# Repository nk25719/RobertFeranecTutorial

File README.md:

# Summary

HOMEWORK 1 

I am learning to use KiCAd.   
I have made my first PCB in KiCad by following Robert's Feranec tutorial. This PCB lights up an LED. 

## Details
* This project has no firmware.
* An printed circuit assembly where a LED can be lit.
* I am following a Tutorial by Robert Feranec.  See: https://youtu.be/maaBkw7IRUc?si=Xxvh67IJcYb2y9pr  
* I learned how to make schematic symbols
* I learned how to make PCB footprints.
* I learned how to make local schematic symbol library.
* I learned how to make local PCB footrpint library.
* I learned how to switch layers for placing traces.

## Instructions 
### Tools list:
* tweeezers
* Ring magnifying 
* soldeting iron
* assembly surface 
* solder
* pen, (sharpies, that can write on the PCB.)

### Detailed Assembly Instructions
* Write a serial nummber on the board.
* Use tweezers to place SMT parts on their footprints and, solder.
* PLace the header pins into the holes of the printed circuit board and turn it upside down and solder from the bottom side.
  
### Instruction for connection for microcontroller kit
* Connect pin 1 of the connector to GPIO pin.
* Connect pin 2 to GND.
* Firmware makes GPIO pin high to turn on LED.

## License   
* Firmware: Affero GPL 3.0
* CERN Open Hardware Licence Version 2 - Strongly Reciprocal

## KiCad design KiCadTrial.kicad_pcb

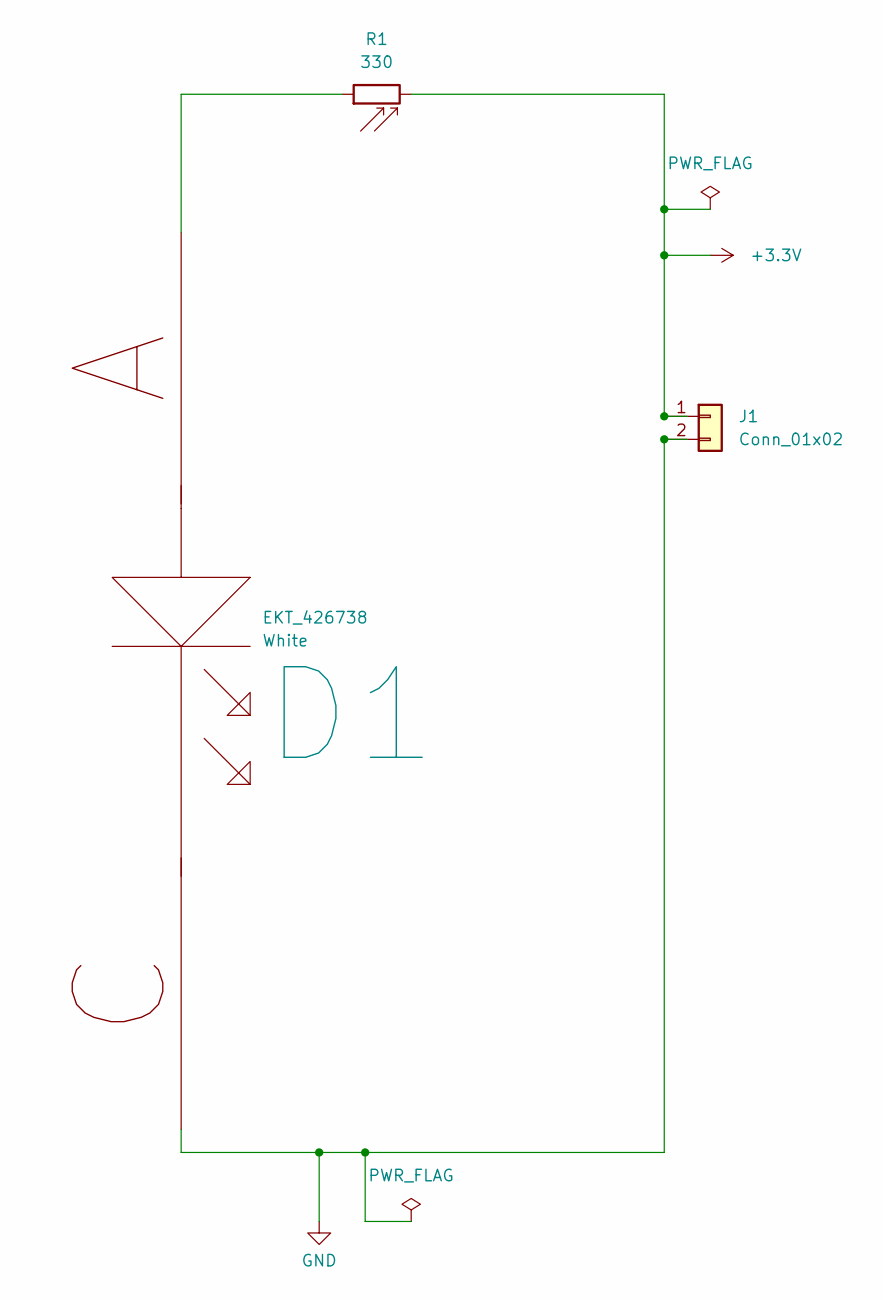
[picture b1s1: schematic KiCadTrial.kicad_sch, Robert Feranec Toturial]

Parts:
D1: White; LED0603; MPN XL-1608SYGC-06; JLCPCB C965805
J1: Conn_01x02; Molex_KK-254_AE-6410-02A_1x02_P2.54mm_Vertical; MPN 2.54-1*2; JLCPCB C5116481
R1: 330; R_0805_2012Metric; MPN 0603WAF3300T5E; JLCPCB C23138

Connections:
+3.3V: J1.1, R1.2
GND: D1.C (Cathode), J1.2
unnamed: D1.A (Anode), R1.1

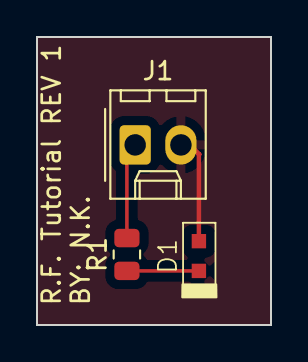
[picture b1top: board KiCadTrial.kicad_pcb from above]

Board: 2 copper layers, 13.0 x 16.0 mm, 3 parts (0 on the bottom side), 3 nets.

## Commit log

2024-03-16 Second Commit
    Adding KiCad files
2024-03-16 Initial PCB Routing
    Placed component on grid.
    Routed copper on the front layer.
    Defined a board outline.
2024-03-16 Changes by Lee.
2024-03-16 Add ground fill to the Front Copper
2024-03-16 JLCPCB PN
    added JLCPCB PN to all components.
2024-03-19 Design for manufacture
    Added board description, version, and a space/place for the SN
2024-03-19 Conn V2
    numbered the pins of the connector on the bottom silkscreen layer
2024-04-06 Update README.md
    Improve description of what was learned from Robert.
2024-04-16 License statement added I coppied it from this other project https://github.com/nk25719/KiCad-esp32-6leds-2switches-1pj-circuit
2024-04-16 Added to the README.md an empty line when the file was saved.
2024-04-16 Update README.md
    We added Instructions.
2024-04-19 Update README.md
    Summary updated
2024-04-19 This change is made with bash
2024-04-19 Led polarity correction
    changed the polarity of the led connected between the resistor and the gnd
2024-06-02 added gbr pos and drl files.
